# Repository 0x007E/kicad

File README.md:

# KiCAD test repository

The `demo` project is based on a pcb with two transistors (`BC547`).

| Experience | Level |
|:------------|:-----:|
| Soldering   |  |
| Mechanical  |  |

## Downloads

| Type      | File               | Description              |
|:---------:|:------------------:|:-------------------------|
| Schematic | [pdf](https://github.com/0x007E/kicad/releases/latest/download/schematic.pdf) / [cadlab](https://cadlab.io/project/28586/main/files)     | Schematic files          |
| Board     | [pdf](https://github.com/0x007E/kicad/releases/latest/download/pcb.pdf) / [cadlab](https://cadlab.io/project/28586/main/files)     | Board file               |
| Drill     | [pdf](https://github.com/0x007E/kicad/releases/latest/download/drill.pdf) | Drill file               |
| BoM | [xlsx](https://github.com/0x007E/kicad/releases/latest/download/bom.xlsx) / [html](https://github.com/0x007E/kicad/releases/latest/download/bom.html)          | Bill of Material as Excel/interactive HTML |
| PCB    | [zip](https://github.com/0x007E/kicad/releases/latest/download/kicad.zip) / [tar](https://github.com/0x007E/kicad/releases/latest/download/kicad.tar.gz)    | KiCAD/Gerber/BoM/Drill files       |

## PCB

The circuit board is populated on one side (Top). The best way for soldering is within a standard soldering system.

### Top Layer

### Bottom Layer

## Additional Information

| Type       | Link               | Description              |
|:----------:|:------------------:|:-------------------------|
| BC547 | [pdf](https://www.sparkfun.com/datasheets/Components/BC546.pdf) | NPN Transistor |

---

> IMPORTANT: Third party devices (e.g. switches, batteries, ...) in layout are mostly imported from [GrabCAD](https://grabcad.com/dashboard), [SnapMagic](https://www.snapeda.com/) or [Component Search Engine](https://componentsearchengine.com/).

---

R. GAECHTER

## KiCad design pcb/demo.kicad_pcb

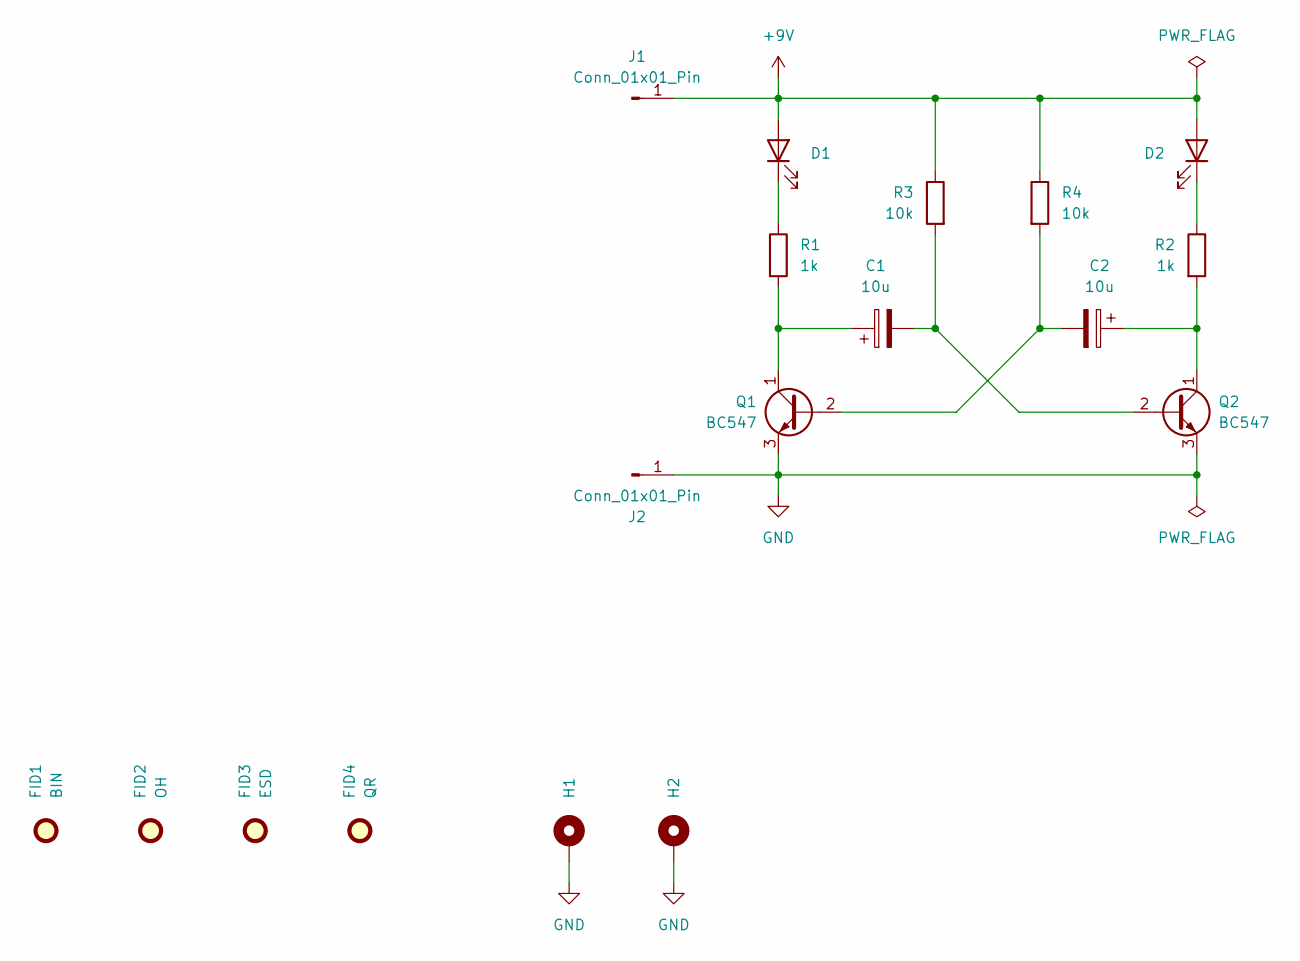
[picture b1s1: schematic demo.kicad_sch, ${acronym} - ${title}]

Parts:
C1, C2: 10u; CP_Radial_D4.0mm_P2.00mm
D1, D2: LED; LED_D5.0mm
FID1: BIN; WEEE-Logo_4.2x6mm_SilkScreen
FID2: OH; OSHW-Logo2_7.3x6mm_SilkScreen
FID3: ESD; ESD-Logo_6.6x6mm_SilkScreen
FID4: QR; QR_0x007e
H1, H2: MountingHole_Pad; MountingHole_3.2mm_M3_DIN965_Pad
J1, J2: Conn_01x01_Pin; PinHeader_1x01_P2.54mm_Vertical
Q1, Q2: BC547; TO-92L_Inline_Wide
R1, R2: 1k; R_Axial_DIN0207_L6.3mm_D2.5mm_P10.16mm_Horizontal
R3, R4: 10k; R_Axial_DIN0207_L6.3mm_D2.5mm_P10.16mm_Horizontal

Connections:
+9V: D1.2 (A), D2.2 (A), J1.1, R3.1, R4.1
GND: H1.1, H2.1, J2.1, Q1.3 (E), Q2.3 (E)
unnamed: D1.1 (K), R1.1
unnamed: D2.1 (K), R2.1
unnamed: C2.2, Q1.2 (B), R4.2
unnamed: C1.1, Q1.1 (C), R1.2
unnamed: C1.2, Q2.2 (B), R3.2
unnamed: C2.1, Q2.1 (C), R2.2

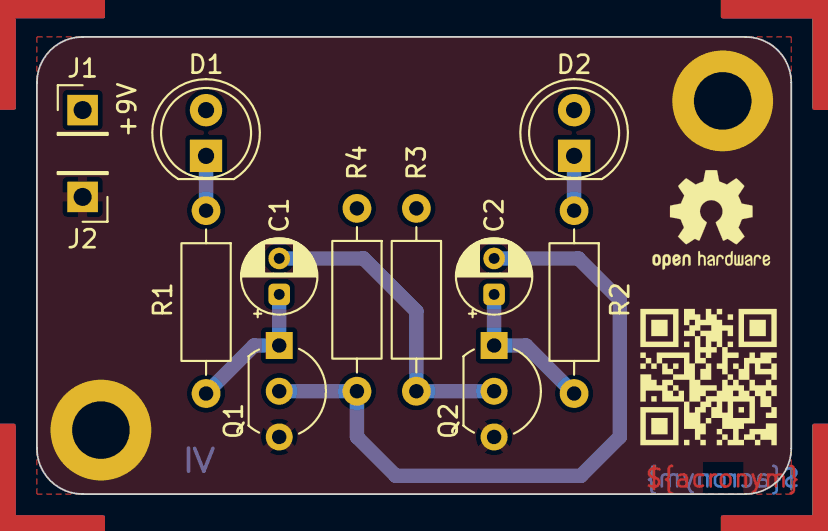
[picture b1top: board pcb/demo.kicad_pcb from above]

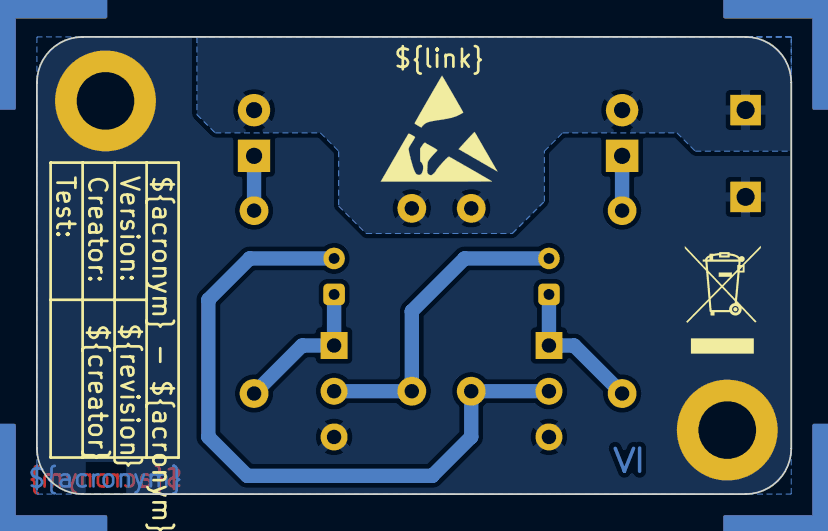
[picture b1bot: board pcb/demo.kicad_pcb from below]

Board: 2 copper layers, 41.9 x 25.4 mm, 18 parts (2 on the bottom side), 8 nets.

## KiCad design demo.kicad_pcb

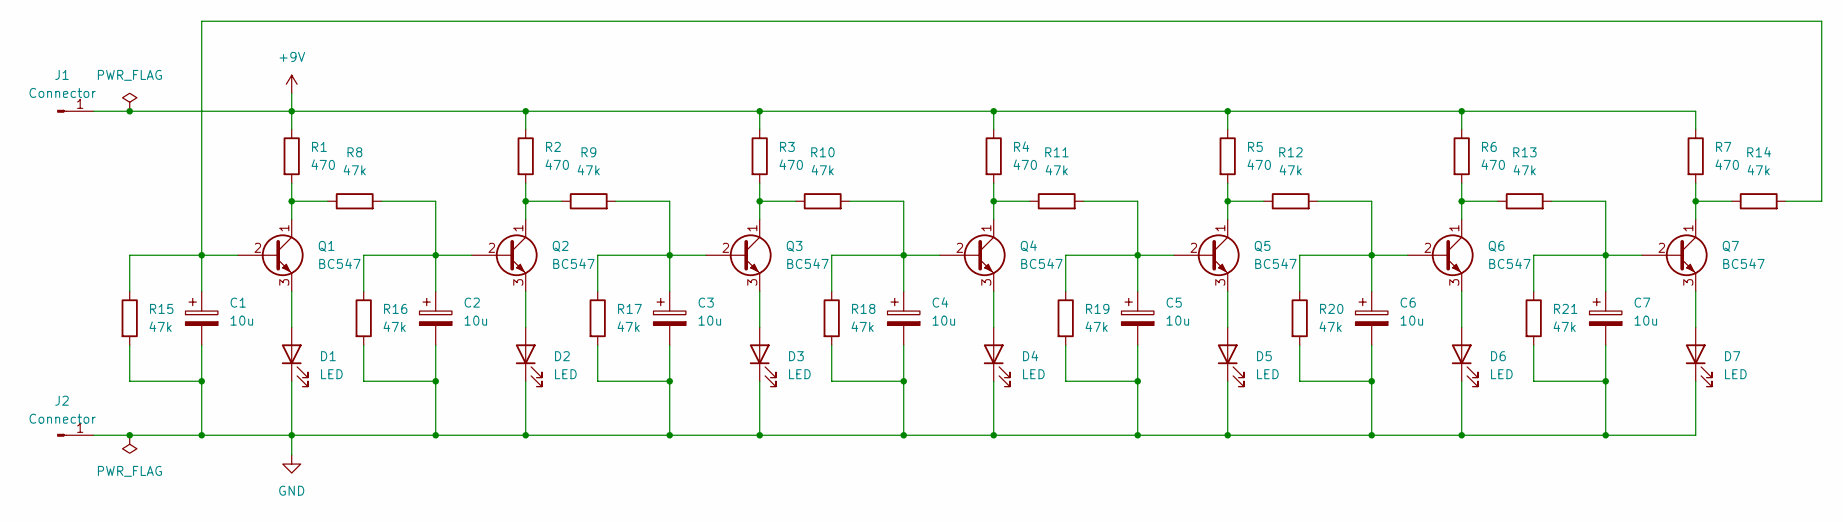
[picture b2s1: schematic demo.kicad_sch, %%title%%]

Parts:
C1, C2, C3, C4, C5, C6, C7: 10u; CP_Radial_D4.0mm_P2.00mm
D1, D2, D3, D4, D5, D6, D7: LED; PinSocket_1x02_P2.54mm_Vertical
J1, J2: Connector; Pin_D1.4mm_L8.5mm_W2.8mm_FlatFork
Q1, Q2, Q3, Q4, Q5, Q6, Q7: BC547; TO-92_Inline_Wide
R1, R2, R3, R4, R5, R6, R7: 470; R_Axial_DIN0207_L6.3mm_D2.5mm_P10.16mm_Horizontal
R8, R9, R10, R11, R12, R13, R14, R15, R16, R17, R18, R19, R20, R21: 47k; R_Axial_DIN0207_L6.3mm_D2.5mm_P10.16mm_Horizontal

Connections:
+9V: J1.1, R1.1, R2.1, R3.1, R4.1, R5.1, R6.1, R7.1
GND: C1.2, C2.2, C3.2, C4.2, C5.2, C6.2, C7.2, D1.1 (K), D2.1 (K), D3.1 (K), D4.1 (K), D5.1 (K), D6.1 (K), D7.1 (K), J2.1, R15.2, R16.2, R17.2, R18.2, R19.2, R20.2, R21.2
unnamed: C1.1, Q1.2 (B), R14.2, R15.1
unnamed: C2.1, Q2.2 (B), R8.2, R16.1
unnamed: C3.1, Q3.2 (B), R9.2, R17.1
unnamed: C4.1, Q4.2 (B), R10.2, R18.1
unnamed: C5.1, Q5.2 (B), R11.2, R19.1
unnamed: C6.1, Q6.2 (B), R12.2, R20.1
unnamed: C7.1, Q7.2 (B), R13.2, R21.1
unnamed: D1.2 (A), Q1.3 (E)
unnamed: D2.2 (A), Q2.3 (E)
unnamed: D3.2 (A), Q3.3 (E)
unnamed: D4.2 (A), Q4.3 (E)
unnamed: D5.2 (A), Q5.3 (E)
unnamed: D6.2 (A), Q6.3 (E)
unnamed: D7.2 (A), Q7.3 (E)
unnamed: Q1.1 (C), R1.2, R8.1
unnamed: Q2.1 (C), R2.2, R9.1
unnamed: Q3.1 (C), R3.2, R10.1
unnamed: Q4.1 (C), R4.2, R11.1
unnamed: Q5.1 (C), R5.2, R12.1
unnamed: Q6.1 (C), R6.2, R13.1
unnamed: Q7.1 (C), R7.2, R14.1

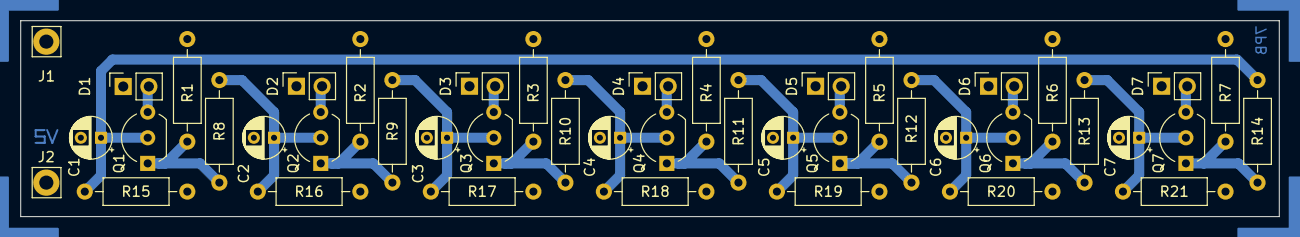
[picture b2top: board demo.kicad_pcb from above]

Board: 2 copper layers, 124.7 x 19.4 mm, 44 parts (0 on the bottom side), 23 nets.

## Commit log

2024-12-01 Add image for preview
2024-12-01 Add values to partlist
2025-01-25 Fix mirror value
2025-01-25 Rename parts of download section
2026-06-20 Update to KiCAD 9
2026-06-21 Rename/Add/Remove bom fields
2026-06-21 Update build pipeline
2026-06-21 Update release pipeline
2026-06-21 Adapt output filenames
2026-06-21 Adapt config and update action versions
2026-06-21 Replace release-creation with gh cli
2026-06-21 Add value to bom

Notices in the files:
README.md:
License CC By-NC-SA
parts and their libraries:
license: CC BY-NC-SA 4.0
